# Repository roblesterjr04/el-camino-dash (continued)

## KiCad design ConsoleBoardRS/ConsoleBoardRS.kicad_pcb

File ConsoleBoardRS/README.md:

# Console board, RetroSound knobs

A variant of the [console board](../ConsoleBoard/) (CAN node `0x13`) for a housing **111.5 × 38.5 mm outside**, with
the controls on two **RetroSound 258A-style knobs** (each an encoder with push, inside a ring that pushes left or
right) on RJ9 (4P4C) cables instead of keys on the board. Same ESP32-S3, the same **SSD1322 256 × 64 OLED** module
(100 × 33.5 mm) on the same 2 × 8 socket, CAN, USB-C and an IR receiver (a TSOP4838 on the board); no keys and no key LEDs.

| Files | |
| --- | --- |
| `ConsoleBoardRS.kicad_sch` / `.kicad_pcb` / `.kicad_pro` | The board: 108.0 × 35.0 mm, **2 layers** (since 2026-10-26; 4 before), SMD on the back only, the OLED socket and IR receiver on the front. KiCad 10 |
| `ConsoleBoardRS.pretty` | The Assmann WSW A-2014-3-4-N-T-R RJ9 footprint (from the Assmann drawing, see [Mechanics](#mechanics)). Everything else is stock KiCad |
| `generate/` | `gen_footprints.py`, `gen_sch.py`, `gen_pcb.py`, `drc.py` (see [Regenerating](#regenerating)) |
| `ConsoleBoardRS_BOM.csv`, `fab/` | BOM, Gerbers / drill, placement and centroid, PCBWay BOM |

**Status:** the current console board; on the panel ([`Panel/README.md`](../Panel/README.md)). Ordered or built: not stated.

**Firmware:** [`firmware/esp32s3_console/`](../firmware/esp32s3_console/README.md).

## Mechanics

```
                                 108.0 mm
   +----o------------------------------------------------------o----+  ---   module flush with the top edge
   |                                                          ::    |
   |                 OLED module 100 x 33.5                   ::    |  35.0  centred left to right (4 mm each side)
   |                 (on standoffs, o = M2 holes)             ::    |
   +123------------------------------------------------------o----+  ---   1.5 mm of board below the module
    J6: the IR receiver, pins 1-2-3 (no hole in that corner)
```

- **Housing:** the board is 108.0 × 35.0 mm, so the 111.5 × 38.5 housing has 1.5 mm walls with 0.25 mm clearance
  all round. The module is centred left to right and **flush with the board's top edge**, as high as the housing
  allows: its top is 1.75 mm below the housing's top outside edge and its bottom 3.25 mm above the bottom outside edge,
  which gives the bezel its text band below the screen. The module's top holes are 2.75 mm from the board's top
  edge, so the M2 standoffs (about 4 mm across the flats) end about 0.5 mm from it.
- **Module:** as on `ConsoleBoard` (`generate/gen_pcb.py` keeps the same parameters), except the right-hand holes,
  checked against the module: H1 at (7.0, 2.75), H2 at (102.0, 2.75), H4 at (102.0, 31.75) mm from the board's top-left
  corner (`R_HOLES_DX`, `H4_DY`: H2 and H4 1 mm right of the 94 × 28 pattern, H4 also 1 mm down). J1 a female 2 × 8
  socket on the old right-hand holes' line (x = 101) shifted 0.5 mm toward the edge (columns at 100.23 and 102.77),
  module pin *n* on socket pad 17 − *n*. Everything is moved 4 mm right (`MX`); `MY` = 0.
- **Front** (module side): J1, three M2 holes (H1, H2, H4) and the IR receiver (J6), nothing else. **Back:** the ESP32
  module (antenna on the top edge), RESET / BOOT, USB-C, the CAN cable, the two RJ9 jacks and all the passives. CAN
  (J3, under the ESP32) and USB-C (J2) are on the bottom edge; the two knob jacks (J4 Select, J5 Volume) face out of
  the back.
- **IR receiver:** J6 is a Vishay TSOP4838 (38 kHz, MOLD package, KiCad `OptoDevice:Vishay_MOLD-3Pin`) on the front in
  the bottom-left corner, where the module's fourth standoff (H3) was: that hole is gone, so the module rests on three.
  Seen from the front its pins read 1-2-3 left to right, **1 signal (IR_IN, GPIO 39, 10k pull-up R10), 2 GND,
  3 VIN (+3V3 through Vishay's supply filter: R11 100 R in series, C16 100 nF to GND, both on the back beside it)**, the TSOP's own order, so it goes straight in. The pins sit 1 mm in from the corner both ways
  (`IR_INSET`): pin 3 at x = 8.0 mm (1 mm right of H3's old centre), the row at y = 32.85 mm (the pads end 1.25 mm from
  the bottom edge, 0.65 mm above the module's bottom edge, so pins 2 and 3 are under the module's corner). Its body
  reaches the bottom edge, so only an "S G V" caption marks it. Assembled with the rest (in the BOM and the placement
  files since 2026-10-23), like its filter (R11, C16) and pull-up (R10).
- **CAN connector:** J3 is a **vertical (top-entry)** JST PH, B4B-PH-K, on its own footprint
  (`JST_PH_B4B-PH-K_1x04_P2.00mm_Vertical`), so the plug goes in from behind the board like the knob plugs.
- **RJ9 jacks:** M- **RJ9 jacks:** Assmann WSW A-2014-3-4-N-T-R (DigiKey 2183644; 4P4C, vertical / top entry, 16.38 mm tall, two
  locating pegs), on the back with their openings facing away from the board: the plugs go in from behind, straight
  toward the board. Centre lines at x = 57.0 and 75.0 mm (seen from the front); the bodies end 1 mm above the bottom
  edge. The footprint (`RJ9_Assmann_A-2014-3-4-N-T-R_Vertical`, `gen_footprints.py`) follows Assmann drawing
  ASS 7331 CO rev00: contacts 1-4 = pads 1-4 (pad 1 square), 0.90 mm holes on 1.27 mm staggered in two rows 2.54 apart
  (1 and 3 in the row nearer the pegs), two 3.20 mm unplated peg holes 7.62 apart, 6.35 mm beyond the near row. The
  body is 11.43 × 16.50 mm, from 6.50 mm beyond the pegs to 0.76 mm beyond the far contact row, so it reaches toward
  the bottom edge (`RJ_BODY` in `gen_pcb.py`). It replaced the Molex 95522-2447 (footprint never verified, 112-week
  lead time) on 2026-10-23.cks

As on [`ConsoleBoard`](../ConsoleBoard/README.md#schematic-blocks) (MCU, power, USB, CAN, OLED, IR), except:

| Block | Parts | Notes |
| --- | --- | --- |
| Knobs | J4 Select, J5 Volume: RJ9 4P4C top-entry jacks; contacts 1 and 4 to GND, 2 and 3 to ADC1 with a 33k pull-up + 10 nF each | See [Knobs](#knobs-rj9) |
| Keys, LEDs | None | Back / View, the four key LEDs, Q1 and their resistors are gone |

### Pins

| ESP32 GPIO | Signal | ESP32 GPIO | Signal |
| --- | --- | --- | --- |
| 12 / 11 / 10 | OLED SCK / MOSI / CS | 1 / 2 | Select knob, jack contacts 2 / 3 (ADC1) |
| 9 / 8 | OLED D/C / RST | 4 / 7 | Volume knob, jack contacts 2 / 3 (ADC1) |
| 5 / 6 | CAN TX / RX | 39 | IR in |
| 19 / 20 | USB D- / D+ | | |

GPIO 13-18, 21, 38, 47 and 48 are free. The console firmware
([`firmware/esp32s3_console/`](../firmware/esp32s3_console/README.md)) reads the knobs on the ADC and draws two
soft-key labels in the screen's bottom corners, used with the right knob's ring (left / right).

## Knobs (RJ9)

The knobs are RetroSound 258A-style dual controls (inner encoder with push, outer three-position ring), measured in
[gpiozero discussion #1119](https://github.com/gpiozero/gpiozero/discussions/1119). Each has a 4-wire RJ9 (4P4C) lead:

| Jack contact | Wire | Inside the knob |
| --- | --- | --- |
| 1 | Black | Ground |
| 2 | Red | Encoder: to ground through open, 82k, 30k (82k ∥ 47k), 47k, open as it turns one way (the reverse the other way). Open and 30k are the detents, so it is a 2-bit Gray code with two steps per detent |
| 3 | Green | Switches: open (none), 6.8k (outer ring left), 22k (outer ring right), 0 Ω (inner push) |
| 4 | Yellow | Ground (0 Ω to black inside the knob, so never power it) |

Contacts 2 and 3 each have a 33k pull-up to 3.3 V and 10 nF to ground, and go to ADC1 (12 dB attenuation). The
levels:

| Green | Volts | Red | Volts |
| --- | --- | --- | --- |
| push (0 Ω) | 0.00 | 30k (detent) | 1.57 |
| outer left (6.8k) | 0.56 | 47k | 1.94 |
| outer right (22k) | 1.32 | 82k | 2.35 |
| none (open) | 3.30 | open (detent) | 3.30 |

The two lines are wired identically on purpose: a reversed phone cord (the usual kind) swaps black with yellow, which
does nothing, and red with green. The firmware tells them apart by their levels (only the encoder ever reads 1.5 to
2.4 V; only the switches read below 1.4 V) and remembers which is which. Sample each line at 1 kHz or so; the 10 nF
settles in about 1.7 ms (5 τ with 33k), well inside one step of a quickly turned knob.

J3 (cable to the DigiDash board): 1 +5 V, 2 CANH, 3 CANL, 4 GND (the cable-port order, see
`docs/hardware/accessory_ports.md`).

## Regenerating

KiCad 10 with its stock libraries, numpy in KiCad's Python (`$KIPY -m pip install --user numpy`) and Freerouting
1.9.0 (Java 17 or newer, opens its window while it routes):

```bash
KIPY=/Applications/KiCad/KiCad.app/Contents/Frameworks/Python.framework/Versions/Current/bin/python3
python3 generate/gen_footprints.py                             # ConsoleBoardRS.pretty
python3 generate/gen_sch.py                                    # also writes generate/refs.json
JAVA=/opt/homebrew/opt/openjdk@17/bin/java $KIPY generate/gen_pcb.py --route freerouting.jar
python3 generate/drc.py
python3 ../tools/fab_export.py ConsoleBoardRS
```

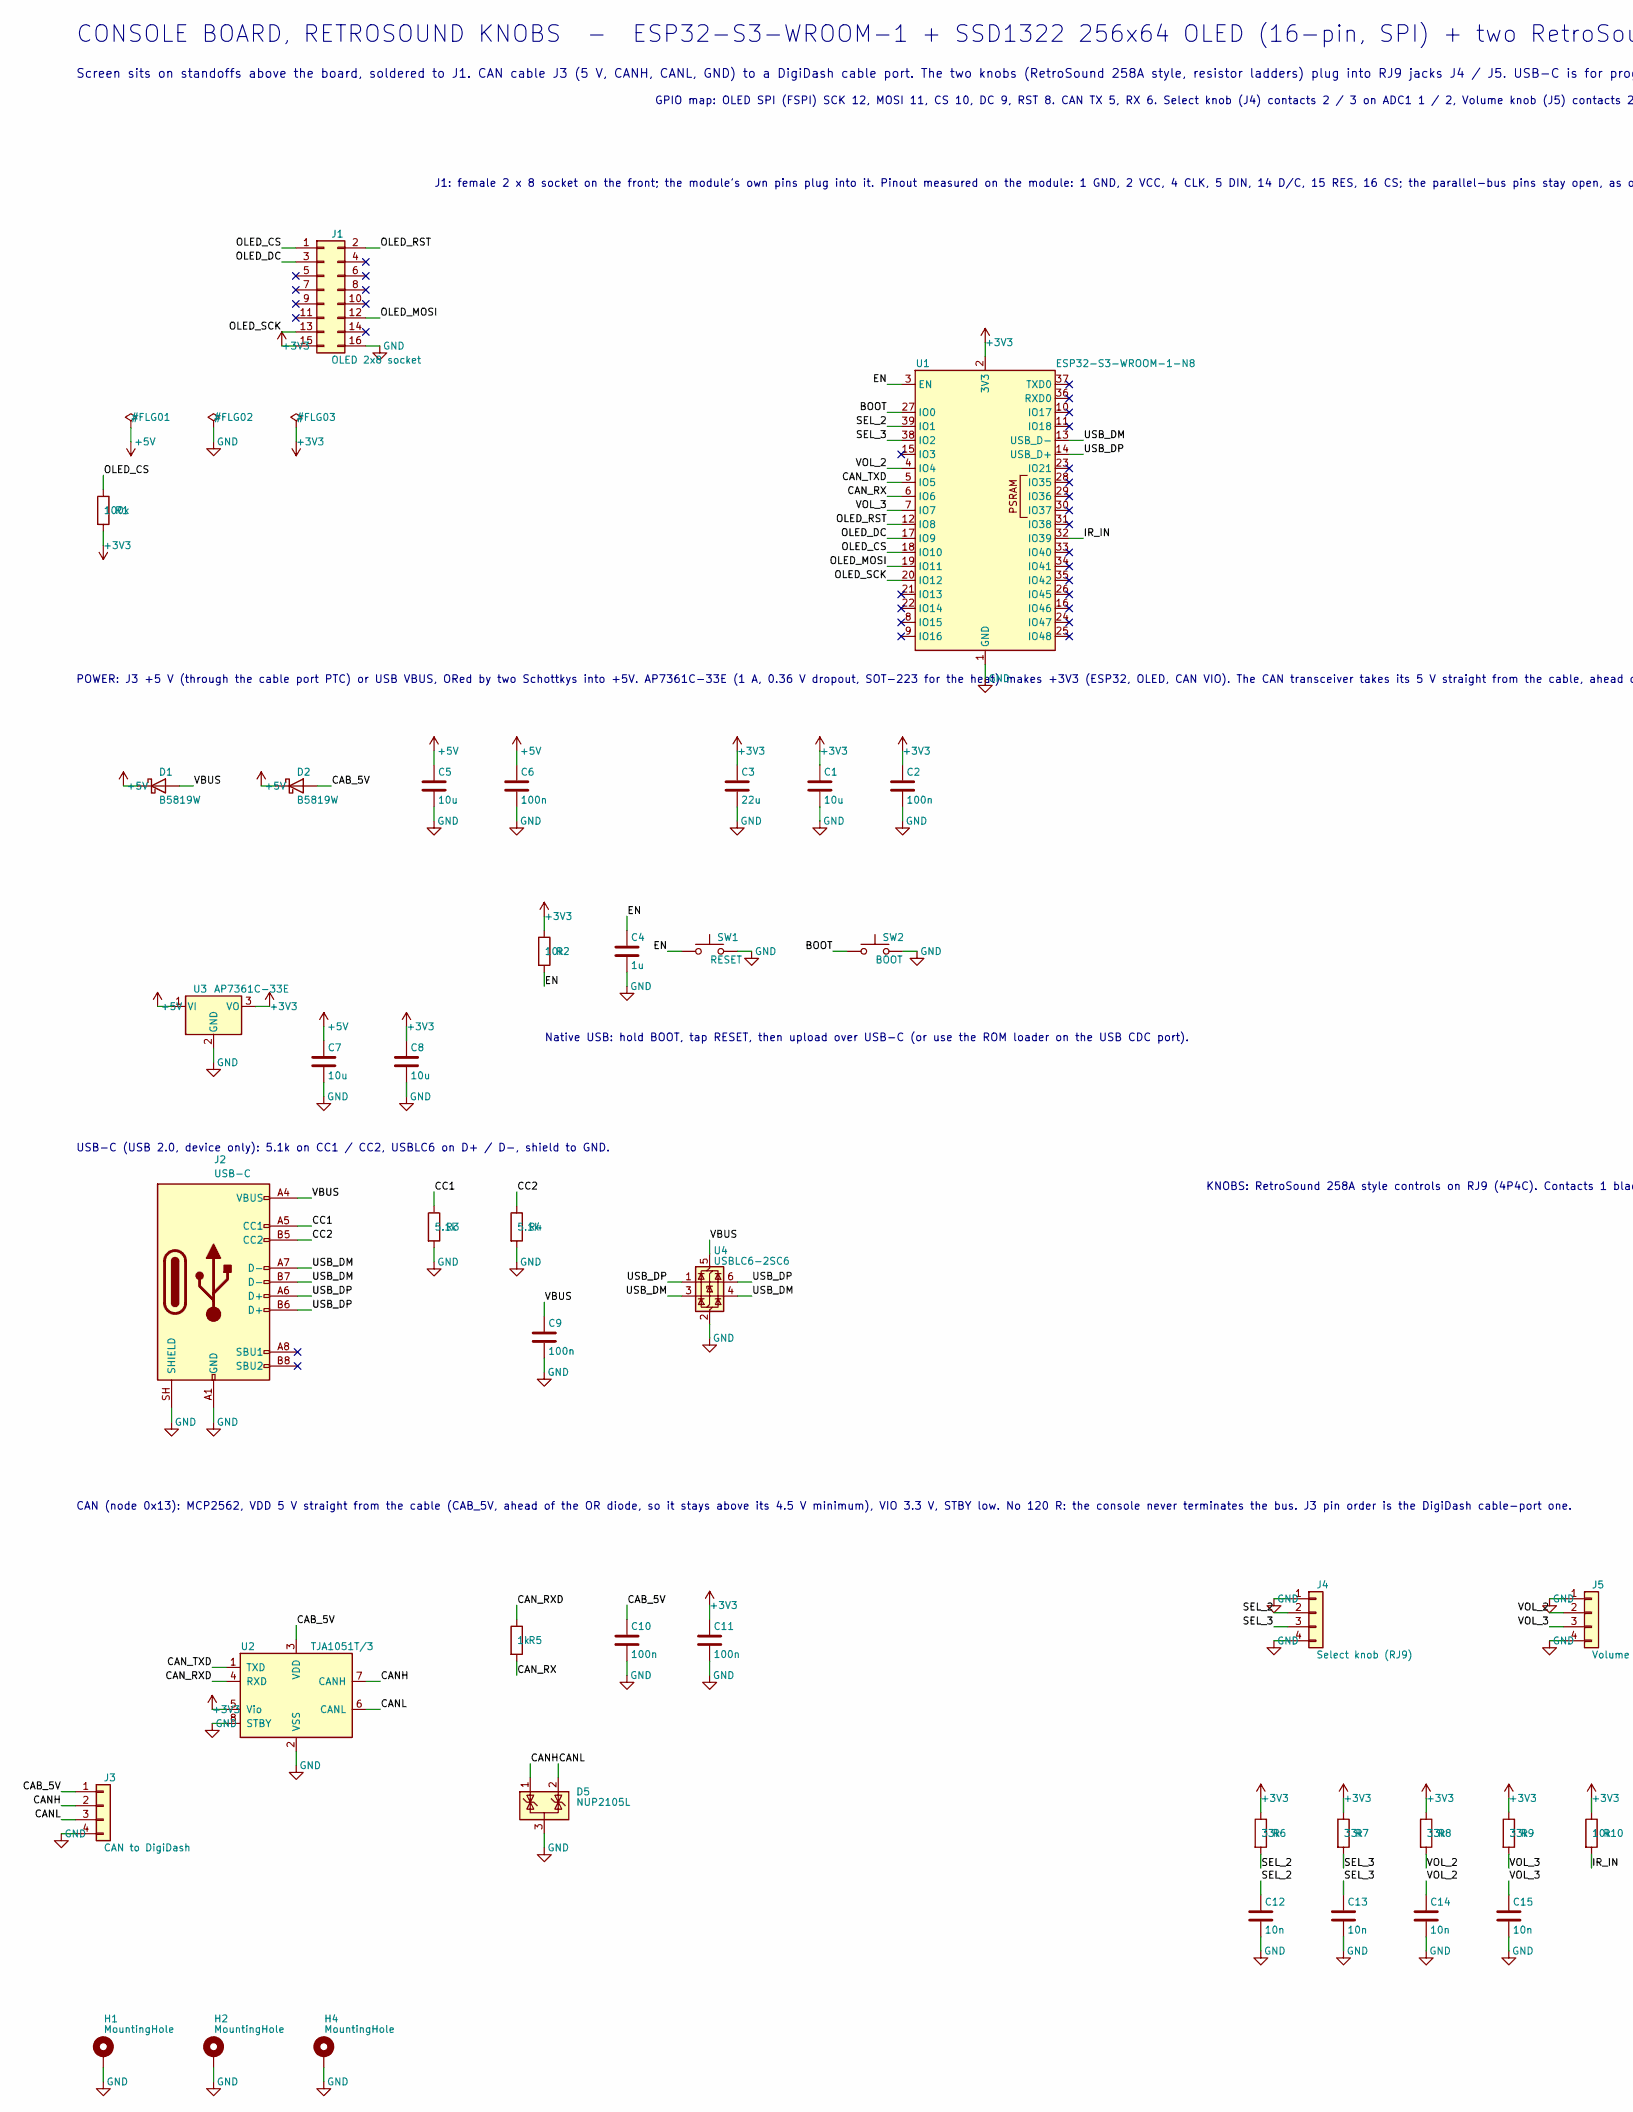
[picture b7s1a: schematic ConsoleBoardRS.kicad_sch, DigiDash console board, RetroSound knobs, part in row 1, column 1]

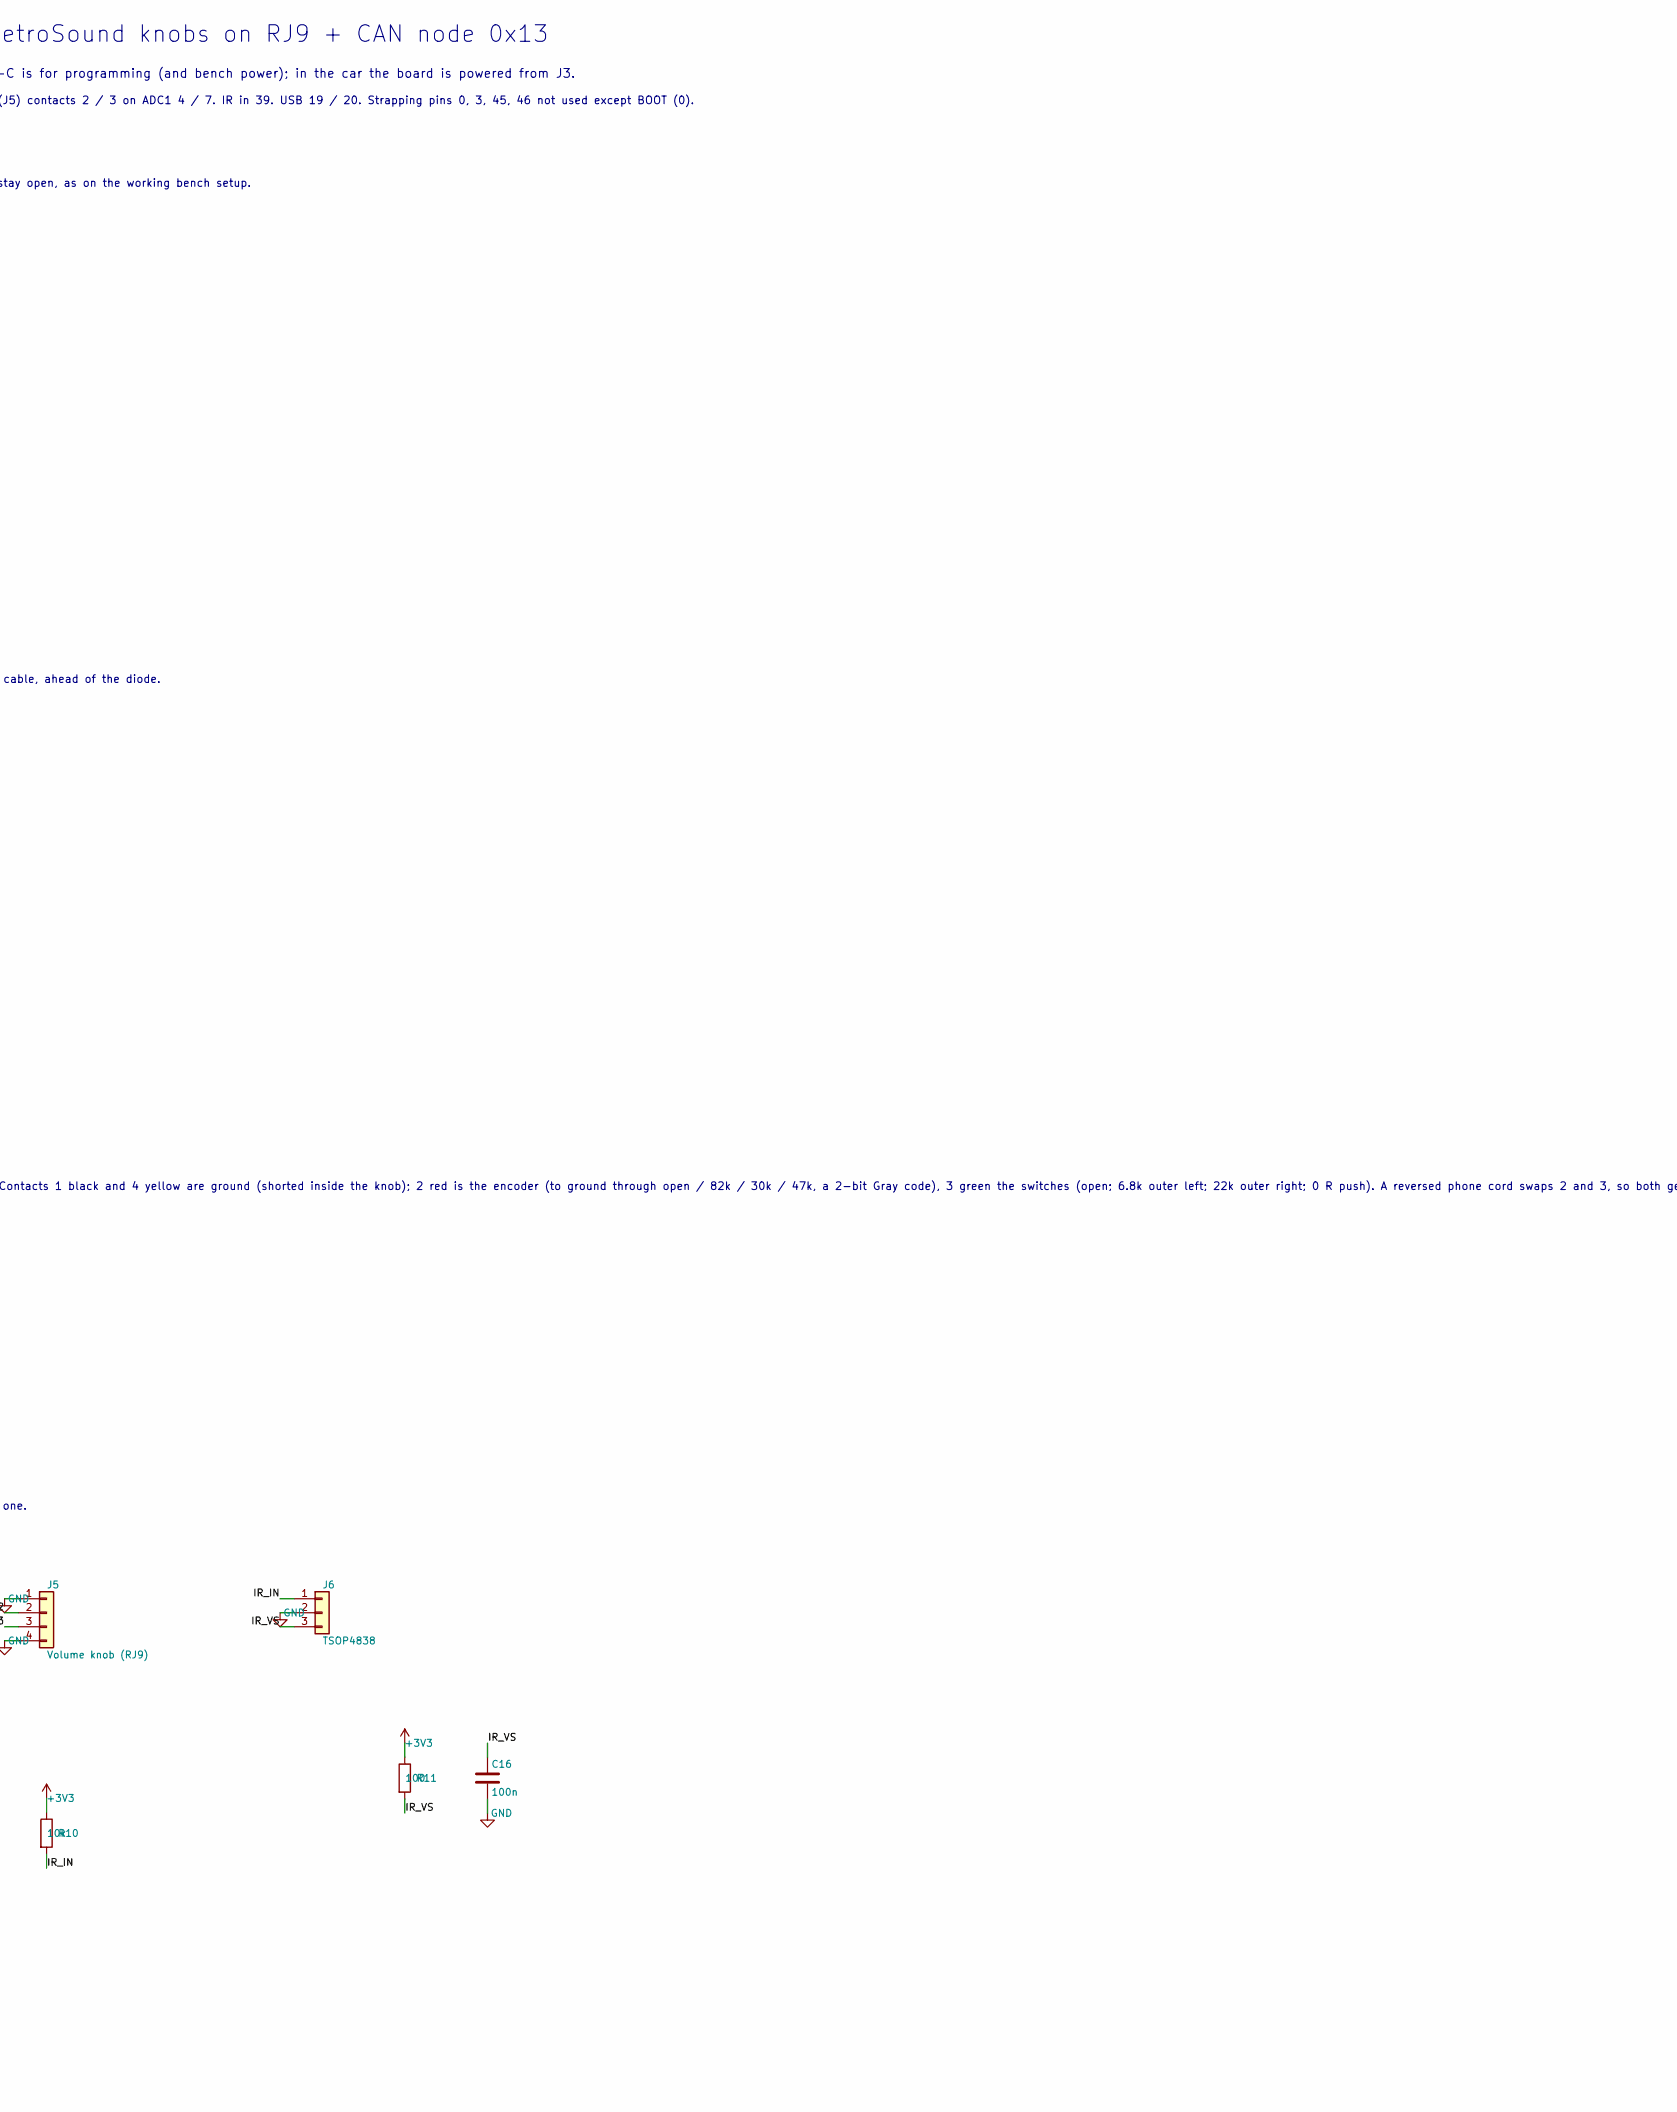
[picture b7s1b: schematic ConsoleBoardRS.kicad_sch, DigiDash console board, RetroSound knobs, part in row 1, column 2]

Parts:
C1, C5, C7, C8: 10u; C_0805_2012Metric
C2, C6, C9, C10, C11, C16: 100n; C_0603_1608Metric
C3: 22u; C_0805_2012Metric
C4: 1u; C_0603_1608Metric
C12, C13, C14, C15: 10n; C_0603_1608Metric
D1, D2: B5819W; D_SOD-123
D5: NUP2105L; SOT-23
H1, H2, H4: MountingHole; MountingHole_2.2mm_M2_Pad
J1: OLED 2x8 socket; PinSocket_2x08_P2.54mm_Vertical
J2: USB-C; USB_C_Receptacle_GCT_USB4105-xx-A_16P_TopMnt_Horizontal
J3: CAN to DigiDash; JST_PH_B4B-PH-K_1x04_P2.00mm_Vertical
J4: Select knob (RJ9); RJ9_Assmann_A-2014-3-4-N-T-R_Vertical
J5: Volume knob (RJ9); RJ9_Assmann_A-2014-3-4-N-T-R_Vertical
J6: TSOP4838; Vishay_MOLD-3Pin
R1: 100k; R_0603_1608Metric
R2, R10: 10k; R_0603_1608Metric
R3, R4: 5.1k; R_0603_1608Metric
R5: 1k; R_0603_1608Metric
R6, R7, R8, R9: 33k; R_0603_1608Metric
R11: 100; R_0603_1608Metric
SW1: RESET; SW_SPST_PTS810
SW2: BOOT; SW_SPST_PTS810
U1: ESP32-S3-WROOM-1-N8; ESP32-S3-WROOM-1
U2: TJA1051T/3; SOIC-8_3.9x4.9mm_P1.27mm
U3: AP7361C-33E; SOT-223-3_TabPin2
U4: USBLC6-2SC6; SOT-23-6

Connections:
+3V3: C1.1, C2.1, C3.1, C8.1, C11.1, J1.15, R1.2, R2.1, R6.1, R7.1, R8.1, R9.1, R10.1, R11.1, U1.2 (3V3), U2.5 (Vio), U3.3 (VO)
+5V: C5.1, C6.1, C7.1, D1.1 (K), D2.1 (K), U3.1 (VI)
/BOOT: SW2.1, U1.27 (IO0)
/CAB_5V: C10.1, D2.2 (A), J3.1, U2.3 (VDD)
/CANH: D5.1 (K), J3.2, U2.7 (CANH)
/CANL: D5.2 (K), J3.3, U2.6 (CANL)
/CAN_RX: R5.2, U1.6 (IO6)
/CAN_RXD: R5.1, U2.4 (RXD)
/CAN_TXD: U1.5 (IO5), U2.1 (TXD)
/CC1: J2.A5 (CC1), R3.1
/CC2: J2.B5 (CC2), R4.1
/EN: C4.1, R2.2, SW1.1, U1.3 (EN)
/IR_IN: J6.1, R10.2, U1.32 (IO39)
/IR_VS: C16.1, J6.3, R11.2
/OLED_CS: J1.1, R1.1, U1.18 (IO10)
/OLED_DC: J1.3, U1.17 (IO9)
/OLED_MOSI: J1.12, U1.19 (IO11)
/OLED_RST: J1.2, U1.12 (IO8)
/OLED_SCK: J1.13, U1.20 (IO12)
/SEL_2: C12.1, J4.2, R6.2, U1.39 (IO1)
/SEL_3: C13.1, J4.3, R7.2, U1.38 (IO2)
/USB_DM: J2.A7 (D-), J2.B7 (D-), U1.13 (USB_D-), U4.3 (I/O2), U4.4 (I/O2)
/USB_DP: J2.A6 (D+), J2.B6 (D+), U1.14 (USB_D+), U4.1 (I/O1), U4.6 (I/O1)
/VBUS: C9.1, D1.2 (A), J2.A4 (VBUS), J2.A9 (VBUS), J2.B4 (VBUS), J2.B9 (VBUS), U4.5 (VBUS)
/VOL_2: C14.1, J5.2, R8.2, U1.4 (IO4)
/VOL_3: C15.1, J5.3, R9.2, U1.7 (IO7)
GND: C1.2, C2.2, C3.2, C4.2, C5.2, C6.2, C7.2, C8.2, C9.2, C10.2, C11.2, C12.2, C13.2, C14.2, C15.2, C16.2, D5.3 (A), H1.1, H2.1, H4.1, J1.16, J2.A1 (GND), J2.A12 (GND), J2.B1 (GND), J2.B12 (GND), J2.SH (SHIELD), J3.4, J4.1, J4.4, J5.1, J5.4, J6.2, R3.2, R4.2, SW1.2, SW2.2, U1.1 (GND), U1.40 (GND), U1.41 (GND), U2.2 (VSS), U2.8 (STBY), U3.2 (GND), U4.2 (GND)

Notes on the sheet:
CONSOLE BOARD, RETROSOUND KNOBS - ESP32-S3-WROOM-1 + SSD1322 256x64 OLED (16-pin, SPI) + two RetroSound knobs on RJ9 + CAN node 0x13
Screen sits on standoffs above the board, soldered to J1. CAN cable J3 (5 V, CANH, CANL, GND) to a DigiDash cable port. The two knobs (RetroSound 258A style, resistor ladders) plug into RJ9 jacks J4 / J5. USB-C is for programming (and bench power); in the car the board is powered from J3.
J1: female 2 x 8 socket on the front; the module's own pins plug into it. Pinout measured on the module: 1 GND, 2 VCC, 4 CLK, 5 DIN, 14 D/C, 15 RES, 16 CS; the parallel-bus pins stay open, as on the working bench setup.
GPIO map: OLED SPI (FSPI) SCK 12, MOSI 11, CS 10, DC 9, RST 8. CAN TX 5, RX 6. Select knob (J4) contacts 2 / 3 on ADC1 1 / 2, Volume knob (J5) contacts 2 / 3 on ADC1 4 / 7. IR in 39. USB 19 / 20. Strapping pins 0, 3, 45, 46 not used except BOOT (0).
Native USB: hold BOOT, tap RESET, then upload over USB-C (or use the ROM loader on the USB CDC port).
POWER: J3 +5 V (through the cable port PTC) or USB VBUS, ORed by two Schottkys into +5V. AP7361C-33E (1 A, 0.36 V dropout, SOT-223 for the heat) makes +3V3 (ESP32, OLED, CAN VIO). The CAN transceiver takes its 5 V straight from the cable, ahead of the diode.
USB-C (USB 2.0, device only): 5.1k on CC1 / CC2, USBLC6 on D+ / D-, shield to GND.
CAN (node 0x13): MCP2562, VDD 5 V straight from the cable (CAB_5V, ahead of the OR diode, so it stays above its 4.5 V minimum), VIO 3.3 V, STBY low. No 120 R: the console never terminates the bus. J3 pin order is the DigiDash cable-port one.
KNOBS: RetroSound 258A style controls on RJ9 (4P4C). Contacts 1 black and 4 yellow are ground (shorted inside the knob); 2 red is the encoder (to ground through open / 82k / 30k / 47k, a 2-bit Gray code), 3 green the switches (open; 6.8k outer left; 22k outer right; 0 R push). A reversed phone cord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

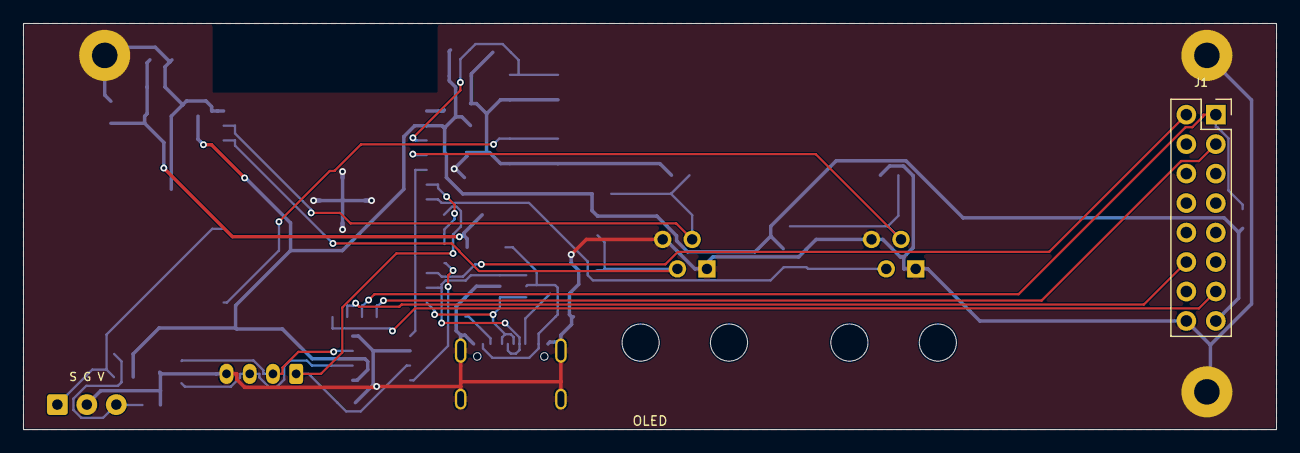
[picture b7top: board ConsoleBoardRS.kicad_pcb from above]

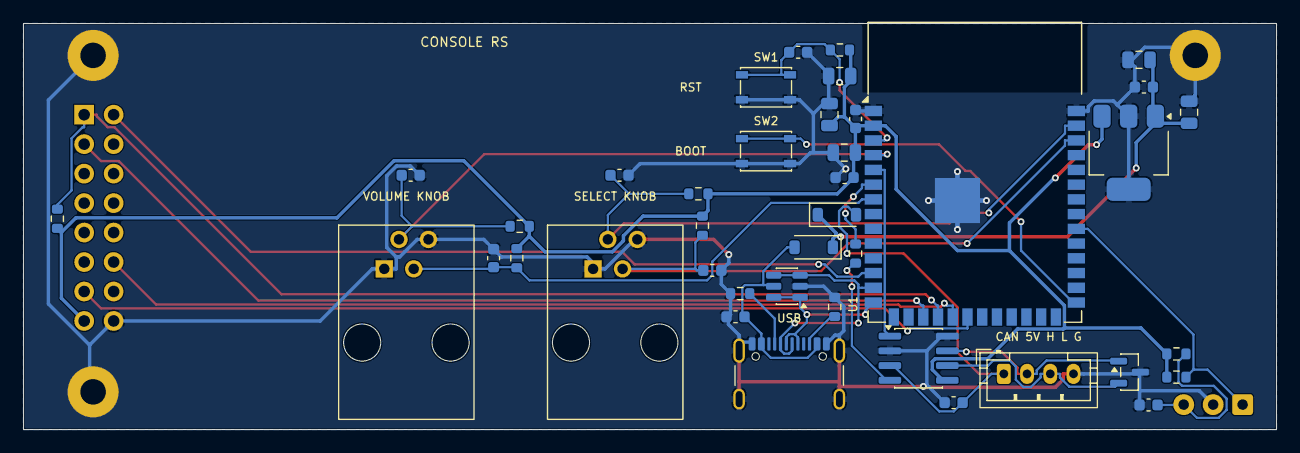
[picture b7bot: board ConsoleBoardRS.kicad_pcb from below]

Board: 2 copper layers, 108.0 x 35.0 mm, 45 parts (40 on the bottom side), 27 nets.

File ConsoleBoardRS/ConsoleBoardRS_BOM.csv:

Qty,Designators,Value,Description,Package / footprint,Manufacturer part (example),Notes
1,U1,ESP32-S3-WROOM-1-N8,"ESP32-S3 module, 8 MB flash, no PSRAM, PCB antenna",RF_Module:ESP32-S3-WROOM-1,Espressif ESP32-S3-WROOM-1-N8,"Antenna on the board edge, keep-out as placed"
1,U2,TJA1051T/3,"CAN FD transceiver (pin-compatible with MCP2562-E/SN), VDD 5 V (from the cable, ahead of the OR diode), VIO 3.3 V",SOIC-8,NXP TJA1051T/3/1J,
1,U3,AP7361C-33E,"LDO 3.3 V 1 A, 0.36 V dropout",SOT-223 (tab = GND),Diodes Inc AP7361C-33E-13,"SOT-223 for the heat: ESP32 + OLED; pinout 1 IN, 2 GND, 3 OUT"
1,U4,USBLC6-2SC6,"USB ESD protection, 2 lines + VBUS",SOT-23-6,STMicroelectronics USBLC6-2SC6,
1,D5,NUP2105L,CAN bus ESD clamp,SOT-23,onsemi NUP2105LT1G,
2,"D1, D2",B5819W,Schottky 40 V 1 A (power OR: USB VBUS and cable 5 V),SOD-123,any B5819W,
1,J1,2x8 female socket,"2.54 mm pin socket, 2 x 8, vertical (OLED module plugs in)",PinSocket_2x08_P2.54mm_Vertical,"any 2.54 mm 2x8 female, about 8.5 mm tall","Wired to the measured module pinout (1 GND, 2 VCC, 4 CLK, 5 DIN, 14 DC, 15 RES, 16 CS)"
1,J2,USB-C,"USB-C receptacle, USB 2.0, 16 pin, top mount",USB_C_Receptacle_GCT_USB4105-xx-A_16P_TopMnt_Horizontal,GCT USB4105-GF-A,
1,J3,JST PH 4-pin,"JST PH 2.0 mm, 4 pin, vertical (top entry), through hole (CAN cable)",JST_PH_B4B-PH-K_1x04_P2.00mm_Vertical,JST B4B-PH-K-S(LF)(SN),Plug goes in from behind the board. Mating housing PHR-4 + SPH-002T-P0.5S crimps
2,"J4, J5",RJ9 4P4C,"Modular jack 4P4C (RJ9), vertical / top entry, through hole (J4 Select knob, J5 Volume knob)",RJ9_Assmann_A-2014-3-4-N-T-R_Vertical (ConsoleBoardRS.pretty),Assmann WSW A-2014-3-4-N-T-R (DigiKey 2183644),"Plugs in from behind the board. 16.38 mm tall, two locating pegs. Footprint from Assmann drawing ASS 7331 CO rev00; pad 1 = jack contact 1"
2,"SW1, SW2",PTS810,"Tact switch 4.2 x 3.2 mm SMT (RESET, BOOT)",SW_SPST_PTS810,C&K PTS810 SJM 250 SMTR LFS,
1,C3,22u,Ceramic X5R 10 V,0805,any,ESP32 bulk
4,"C1, C5, C7, C8",10u,Ceramic X5R 16 V (on +5V / +3V3),0805,any,16 V or 25 V rating keeps capacitance at 5 V (DC bias)
1,C4,1u,Ceramic X7R 16 V,0603,any,EN reset delay (with R2 10k)
6,"C2, C6, C9, C10, C11, C16",100n,Ceramic X7R 50 V,0603,any,C16: IR receiver supply filter (with R11)
4,C12-C15,10n,Ceramic X7R 50 V,0603,any,Knob ladder filtering
2,"R2, R10",10k,Resistor 1 % 1/10 W,0603,any,R2 EN pull-up; R10 IR pull-up
4,R6-R9,33k,Resistor 1 % 1/10 W,0603,any,Knob ladder pull-ups (the same on both lines of each jack)
1,R1,100k,Resistor 1 % 1/10 W,0603,any,OLED CS pull-up
2,"R3, R4",5.1k,Resistor 1 % 1/10 W,0603,any,USB-C CC1 / CC2 (device)
1,R5,1k,Resistor 1 % 1/10 W,0603,any,CAN RXD series
1,R11,100,Resistor 1 % 1/10 W,0603,any,IR receiver supply filter: in series with its VS (with C16)
3,"H1, H2, H4",M2 hole,"Mounting hole 2.2 mm, plated, GND",MountingHole_2.2mm_M2_Pad,none (PCB feature),"Screen standoffs: M2, height to suit J1 plus the module's pins"
